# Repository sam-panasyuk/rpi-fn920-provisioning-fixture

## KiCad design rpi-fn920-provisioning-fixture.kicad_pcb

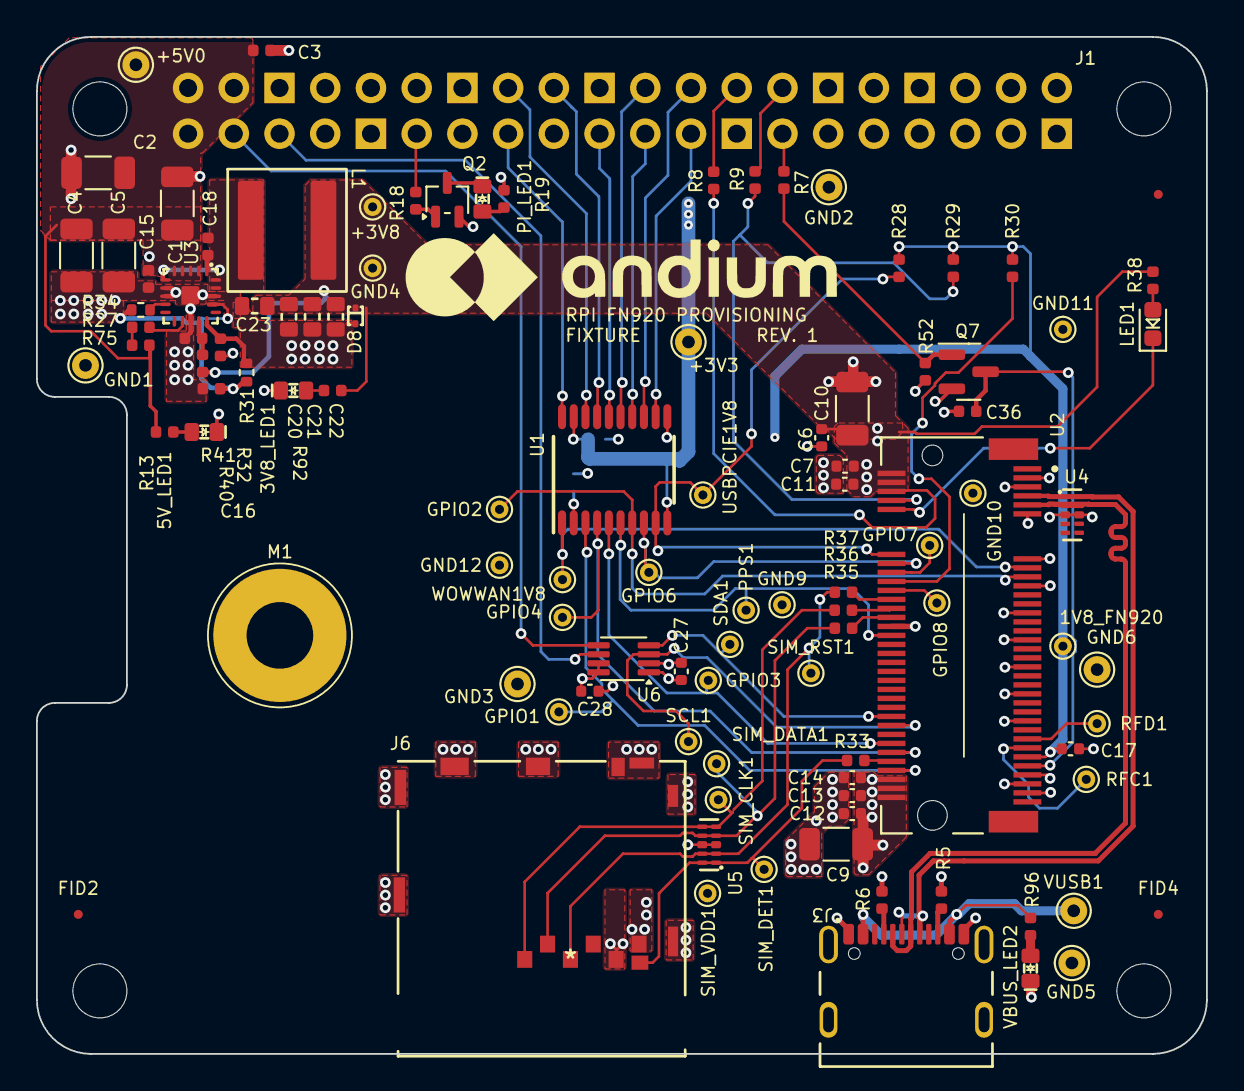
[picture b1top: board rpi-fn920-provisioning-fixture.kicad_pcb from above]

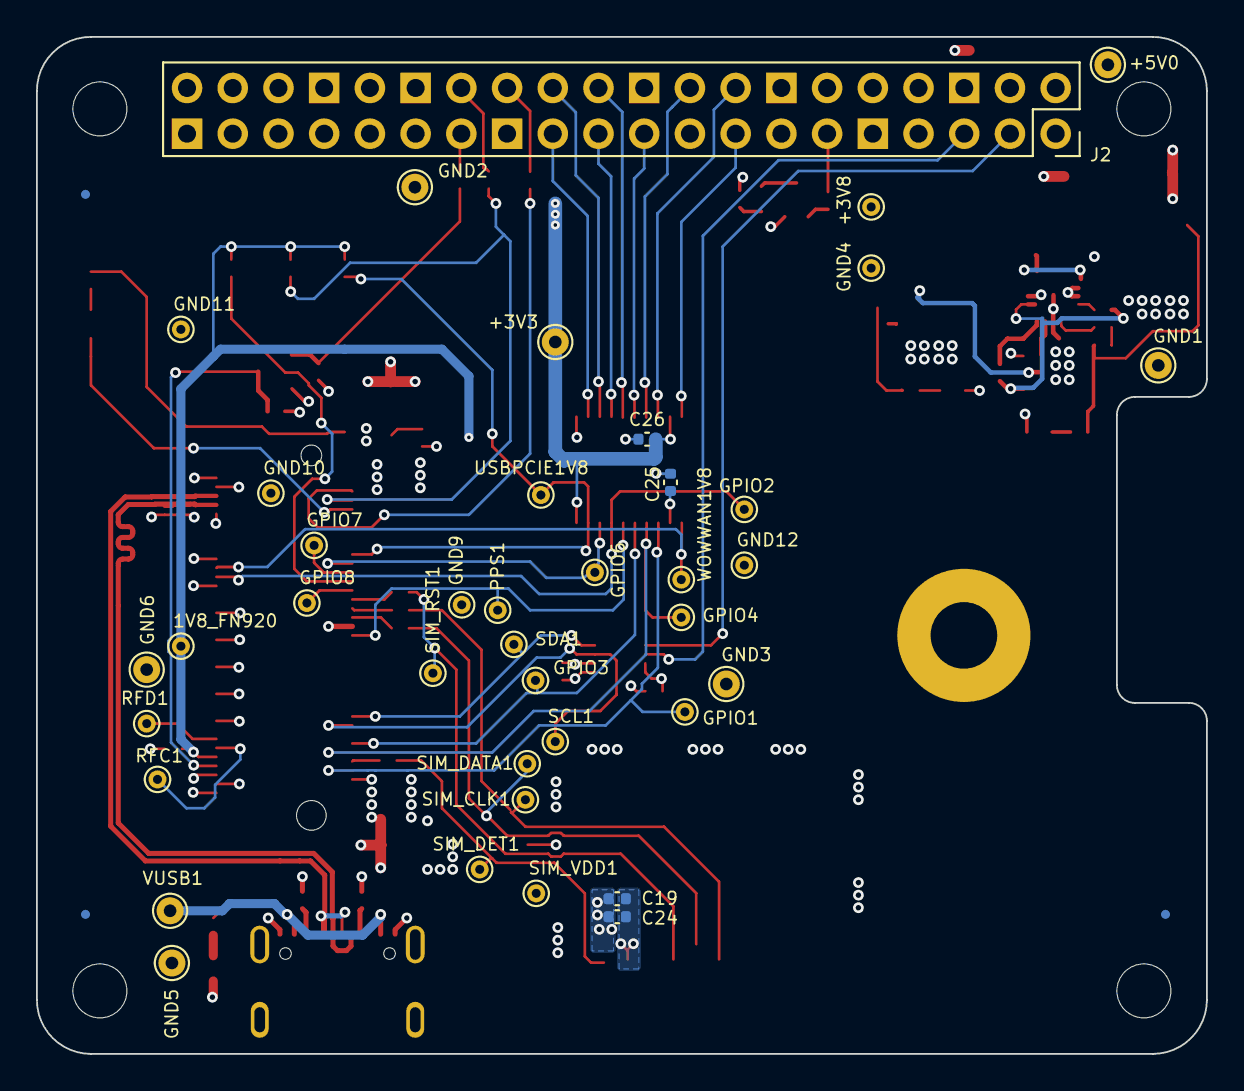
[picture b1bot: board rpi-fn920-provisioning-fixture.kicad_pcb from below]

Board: 4 copper layers, 65.0 x 56.5 mm, 114 parts (8 on the bottom side), 68 nets.

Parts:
1V8_FN920: TP 1mm; TestPoint_THTPad_D1.0mm_Drill0.5mm
3V8_LED1, 5V_LED1: LTST-C190GKT; LED_0603_1608Metric_G
+3V3, +5V0: TestPoint_1.5mm_0.7mm_TH; TestPoint_THTPad_D1.5mm_Drill0.7mm
+3V8: TestPoint_1mm_0.5mm_TH; TestPoint_THTPad_D1.0mm_Drill0.5mm
C1, C2, C4, C5, C9, C10: 100uF 10V X5R; C_1206_3216Metric
C3, C15, C18, C36: 100nF 50V X5R; C_0402_1005Metric
C6, C19: 33pF 50V C0G; C_0402_1005Metric
C7, C11, C12, C13, C14, C17, C25, C26, C27, C28: 100nF 50V X7R; C_0402_1005Metric
C16: 1uF 10V X6S; C_0402_1005Metric
C20, C21, C22, C23: 22uF 16V X5R; C_0603_1608Metric
C24: 220pF 50V C0G; C_0402_1005Metric
D8: ESD9X5.0ST5G; SOD-923
FID1, FID2, FID3, FID4, FID5, FID6: FID_0.5MM_1MM_MASK; Fiducial_0.5mm_Mask1mm
GND1, GND2, GND3, GND5, GND6: TestPoint_1.5mm_0.7mm_TH; TestPoint_THTPad_D1.5mm_Drill0.7mm
GND4: TestPoint_1mm_0.5mm_TH; TestPoint_THTPad_D1.0mm_Drill0.5mm
GND9, GND10, GND11, GND12: TP 1mm; TestPoint_THTPad_D1.0mm_Drill0.5mm
GPIO1, GPIO2, GPIO3, GPIO4, GPIO6, GPIO7, GPIO8: TP 1mm; TestPoint_THTPad_D1.0mm_Drill0.5mm
J1: modul; RPI_Hat_B+
J2: SOCKET 40P 2.54mm PLACEHOLDER; PinSocket_2x20_P2.54mm_Vertical_PLACEHOLDER
J3: USB-C; USB-C_Receptacle_GCT_USB4105-GF-A
J6: 2822541-1; 2822541-1_TEC
L1: 4.7uH 11A; L_Coilcraft-XAL6030
LED1: B1911PG--20D000514U1930; LED_0603_1608Metric
M1: STNDF_M2_2.5MM_9774025243R; MountingHole_3.7mm_Pad
PI_LED1: LTST-C190GKT; LED_0603_1608Metric_G
PPS1: TP 1mm; TestPoint_THTPad_D1.0mm_Drill0.5mm
Q2: NPN 40V 0.2A; SOT-323_SC-70
Q7: N-CH 25V 0.22A; FDV301N
R5, R6: 5k6; R_0402_1005Metric
R7, R8, R9, R27: 0R; R_0402_1005Metric
R13: 3k01; R_0402_1005Metric
R18, R19, R28, R29, R30, R32, R52, R75: 10k; R_0402_1005Metric
R31: 220k; R_0402_1005Metric
R33: 102R; R_0402_1005Metric
R34: 100k; R_0402_1005Metric
R35, R36, R37: 22R1; R_0402_1005Metric
R38: 9k09; R_0402_1005Metric
R40: 80k6; R_0402_1005Metric
R41: 15k; R_0402_1005Metric
R92, R96: 1k62; R_0402_1005Metric
RFC1: TP 1mm; TestPoint_THTPad_D1.0mm_Drill0.5mm
RFD1: TP 1mm; TestPoint_THTPad_D1.0mm_Drill0.5mm
SCL1: TP 1mm; TestPoint_THTPad_D1.0mm_Drill0.5mm
SDA1: TP 1mm; TestPoint_THTPad_D1.0mm_Drill0.5mm
SIM_CLK1: TP 1mm; TestPoint_THTPad_D1.0mm_Drill0.5mm
SIM_DATA1: TP 1mm; TestPoint_THTPad_D1.0mm_Drill0.5mm
SIM_DET1: TP 1mm; TestPoint_THTPad_D1.0mm_Drill0.5mm
SIM_RST1: TP 1mm; TestPoint_THTPad_D1.0mm_Drill0.5mm
SIM_VDD1: TP 1mm; TestPoint_THTPad_D1.0mm_Drill0.5mm
U1: TXB0108PWR
U2: FN920C04-WW; AMPHENOL_MDT420B01001_FN920C04
U3: 12A; QFN-20-1EP_3x3mm_P0.45mm_TPS56xxxx
U4, U5: TVS 14V 2.5A; USON-10_2.5x1mm_P0.5mm
U6: PCA9306; VSSOP-8_2.3x2mm_P0.5mm
USBPCIE1V8: TP 1mm; TestPoint_THTPad_D1.0mm_Drill0.5mm
VBUS_LED2: LTST-C190GKT; LED_0603_1608Metric_G
VUSB1: TestPoint_1.5mm_0.7mm_TH; TestPoint_THTPad_D1.5mm_Drill0.7mm
WOWWAN1V8: TP 1mm; TestPoint_THTPad_D1.0mm_Drill0.5mm

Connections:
+1V8_FN920: 1V8_FN920.1 (1_1), C17.2, C25.1, C27.1, R28.2, R29.2, R30.2, U1.2 (VCCA), U2.65 (1V8_OUT), U6.2 (VREF1)
+3V3: +3V3.1 (1_1), C26.1, C28.1, J1.1 (3.3V), J1.17 (3.3V), R19.2, U1.10 (OE), U1.19 (VCCB), U6.7 (VREF2), U6.8 (EN)
+3V8: +3V8.1 (1_1), C6.1, C7.1, C9.1, C10.1, C11.1, C12.1, C13.1, C14.1, C20.2, C21.2, C22.2, C23.2, D8.1 (C), L1.2, R38.2, R40.1, R92.2, U2.2 (VBAT), U2.4 (VBAT), U2.70 (VBAT), U2.72 (VBAT), U2.74 (VBAT)
+5V: +5V0.1 (1_1), C1.1, C2.1, C3.1, C4.1, C5.1, C15.1, J1.2 (5V), J1.4 (5V), R13.2, R75.2, U3.2 (V_{IN}), U3.3 (V_{IN}), U3.4 (V_{IN}), U3.5 (V_{IN})
/1PPS_1V8: PPS1.1 (1_1), U1.6 (A5), U2.38 (1PPS)
/1PPS_3V3: J1.22 (BCM25), U1.15 (B5)
/3V8_FB: R40.2, R41.2, U3.14 (FB)
/3V8_SW: C18.1, L1.1, U3.6 (SW), U3.19 (SW), U3.20 (SW)
/5V_EN_JMP: R27.2, U3.12 (EN)
/CLK: RFC1.1 (1_1), U2.63 (RFFE0_CLK_)
/DATA: RFD1.1 (1_1), U2.61 (RFFE0_DATA_)
/FN_GPIO1_1V8: GPIO1.1 (1_1), U1.3 (A2), U2.68 (GPIO1)
/FN_GPIO1_3V3: J1.16 (BCM23), U1.18 (B2)
/FN_GPIO2_1V8: GPIO2.1 (1_1), U1.7 (A6), U2.25 (GPIO2)
/FN_GPIO2_3V3: J1.21 (BCM9_MISO), U1.14 (B6)
/FN_GPIO3_1V8: GPIO3.1 (1_1), U1.5 (A4), U2.62 (GPIO3)
/FN_GPIO3_3V3: J1.19 (BCM10_MOSI), U1.16 (B4)
/FN_GPIO4_1V8: GPIO4.1 (1_1), U1.4 (A3), U2.64 (GPIO4)
/FN_GPIO4_3V3: J1.18 (BCM24), U1.17 (B3)
/FN_GPIO6_1V8: GPIO6.1 (1_1), U1.8 (A7), U2.22 (GPIO6)
/FN_GPIO6_3V3: J1.24 (BCM8_CE0), U1.13 (B7)
/FN_GPIO7_1V8: GPIO7.1 (1_1), U2.24 (GPIO7)
/FN_GPIO8_1V8: GPIO8.1 (1_1), U2.28 (GPIO8)
/FULL_OFF_N_3V3: R8.1, U2.6 (FULL_CARD_POWER_OFF)
/LED1: LED1.1 (K), U2.10 (LED1)
/PI_LED1: J1.11 (BCM17), R18.1
/RESET_3V3: Q7.1 (G), R7.1, R52.2
/SCL_1V8: SCL1.1 (1_1), U2.58 (I2C_SCL), U6.3 (SCL1)
/SCL_3V3: J1.5 (BCM3_SCL), U6.6 (SCL2)
/SDA_1V8: SDA1.1 (1_1), U2.56 (I2C_SDA), U6.4 (SDA1)
/SDA_3V3: J1.3 (BCM2_SDA), U6.5 (SDA2)
/SIM_CLK: J6.3 (CLK), R36.2, SIM_CLK1.1 (1_1), U5.5, U5.6
/SIM_DATA: J6.6 (I/O), R35.2, SIM_DATA1.1 (1_1), U5.4, U5.7
/SIM_DET: J6.7 (SW), R33.2, SIM_DET1.1 (1_1), U5.1, U5.10
/SIM_RST: J6.2 (RST), R37.2, SIM_RST1.1 (1_1), U5.2, U5.9
/SIM_VDD: C19.1, C24.1, J6.1 (VCC), SIM_VDD1.1 (1_1), U2.36 (USIM1_VDD)
/USB_PCIE_1V8: R28.1, U1.9 (A8), U2.20 (USB_PCIE_SW), USBPCIE1V8.1 (1_1)
/USB_PCIE_3V3: J1.23 (BCM11_SCLK), U1.12 (B8)
/WOWWAN_1V8: U1.1 (A1), U2.23 (WOWWAN), WOWWAN1V8.1 (1_1)
/WOWWAN_3V3: J1.15 (BCM22), U1.20 (B1)
/W_DISABLE1_N_3V3: R9.1, R29.1, U2.8 (W_DISABLE1)
/W_DISABLE2_N_3V3: R30.1, U2.26 (W_DISABLE2)
/~RESET: C36.2, Q7.3 (D), U2.67 (RESET)
GND: 3V8_LED1.1 (C), 5V_LED1.1 (C), C1.2, C2.2, C3.2, C4.2, C5.2, C6.2, C7.2, C9.2, C10.2, C11.2, C12.2, C13.2, C14.2, C15.2, C16.1, C17.1, C19.2, C20.1, C21.1, C22.1, C23.1, C24.2, C25.2, C26.2, C27.2, C28.2, C36.1, D8.2 (A), GND1.1 (1_1), GND2.1 (1_1), GND3.1 (1_1), GND4.1 (1_1), GND5.1 (1_1), GND6.1 (1_1), GND9.1 (1_1), GND10.1 (1_1), GND11.1 (1_1), GND12.1 (1_1), J1.6 (GND), J1.9 (GND), J1.14 (GND), J1.20 (GND), J1.25 (GND), J1.30 (GND), J1.34 (GND), J1.39 (GND), J3.A1 (GND), J3.A12 (GND), J3.B1 (GND), J3.B12 (GND), J3.SH, J6.4 (GND), J6.9 (GND), J6.10 (GND), J6.11 (GND), J6.12 (GND), J6.13 (GND), J6.14 (GND), J6.15 (GND), J6.16 (GND), M1.1 (1_1), Q2.2 (E), Q7.2 (S), R5.1, R6.1, R32.1, R41.1, R52.1, U1.11 (GND), U2.3 (GND), U2.5 (GND), U2.11 (GND), U2.21 (CONFIG_0_GND), U2.27 (GND), U2.33 (GND), U2.39 (GND), U2.45 (GND), U2.51 (GND), U2.57 (GND), U2.69 (CONFIG_1_GND), U2.71 (GND), U2.73 (GND), U3.7 (PGND), U3.8 (PGND), U3.13 (AGND), U3.18 (PGND), U3.21 (PGND), U4.3, U4.8, U5.3, U5.8, U6.1 (GND), VBUS_LED2.1 (C)
LTE_USB2.0_N: J3.A7 (D_{A}-), J3.B7 (D_{B}-), U2.9 (USB_D-), U4.2, U4.9
LTE_USB2.0_P: J3.A6 (D_{A}+), J3.B6 (D_{B}+), U2.7 (USB_D+), U4.1, U4.10
unnamed: 3V8_LED1.2 (A), R92.1
unnamed: 5V_LED1.2 (A), R13.1
unnamed: J1.27 (BCM0_ID_SD), R7.2
unnamed: J1.28 (BCM1_ID_SC), R9.2
unnamed: J1.26 (BCM7_CE1), R8.2
unnamed: J3.A5 (CC_{1}), R6.2
unnamed: J3.B5 (CC_{2}), R5.2
unnamed: LED1.2 (A), R38.1
unnamed: PI_LED1.2 (A), R19.1
unnamed: PI_LED1.1 (C), Q2.3 (C)
unnamed: Q2.1 (B), R18.2
unnamed: R27.1, R75.1
unnamed: R36.1, U2.32 (USIM1_CLK)
unnamed: R35.1, U2.34 (USIM1_DATA)
unnamed: R33.1, U2.66 (USIM1_DET)
unnamed: R37.1, U2.30 (USIM1_RESET)
unnamed: C18.2, U3.1 (BST)
unnamed: R31.1, R32.2, U3.15 (MODE)
unnamed: R34.2, U3.9 (PG)
unnamed: C16.2, R31.2, R34.1, U3.17 (V_{CC})
unnamed: R96.1, VBUS_LED2.2 (A)
VBUS: J3.A4 (VBUS), J3.A9 (VBUS), J3.B4 (VBUS), J3.B9 (VBUS), R96.2, VUSB1.1 (1_1)

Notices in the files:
parts and their libraries:
License: Apache-2.0
